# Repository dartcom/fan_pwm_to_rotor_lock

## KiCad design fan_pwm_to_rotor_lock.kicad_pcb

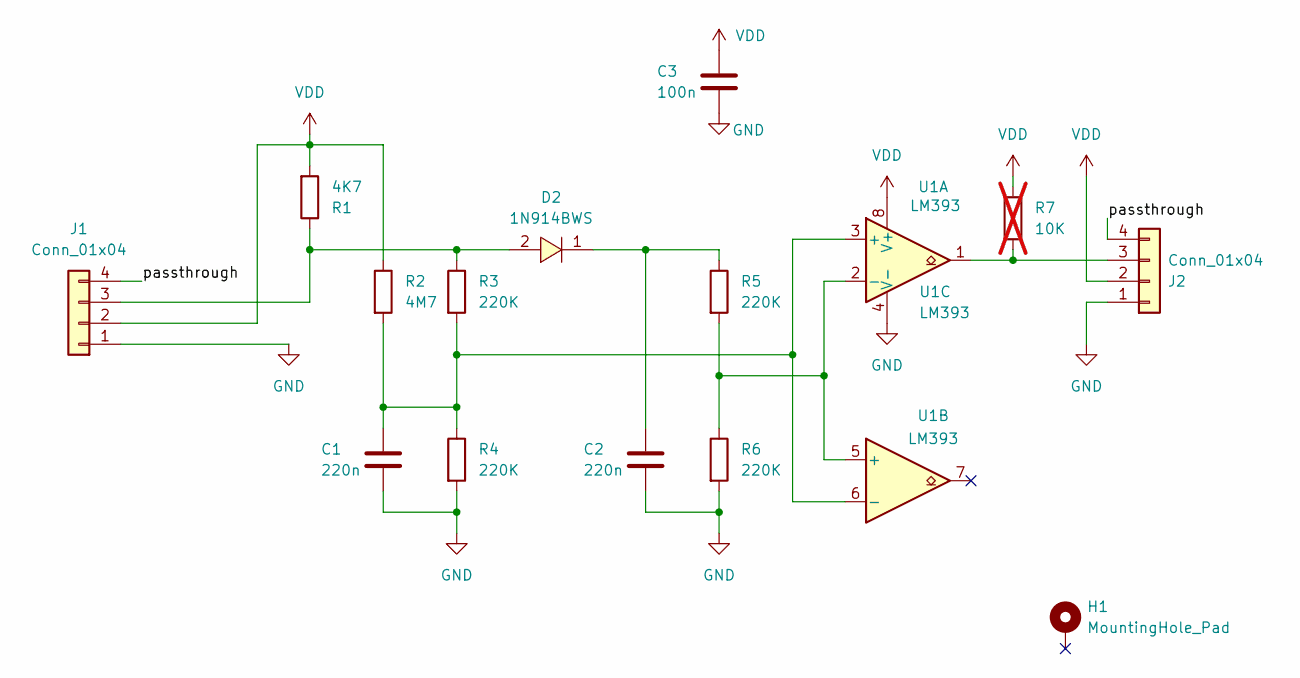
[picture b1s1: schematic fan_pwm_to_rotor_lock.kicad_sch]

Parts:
C1, C2: 220n; C_0805_2012Metric_Pad1.18x1.45mm_HandSolder
C3: 100n; C_0805_2012Metric_Pad1.18x1.45mm_HandSolder
D2: 1N914BWS; D_SOD-323_HandSoldering; LCSC Part C258181
H1: MountingHole_Pad; MountingHole_3.2mm_M3_Pad_Via
J1, J2: Conn_01x04; FanPinHeader_1x04_P2.54mm_Vertical
R1: 4K7; R_0805_2012Metric_Pad1.20x1.40mm_HandSolder
R2: 4M7; R_0805_2012Metric_Pad1.20x1.40mm_HandSolder
R3, R4, R5, R6: 220K; R_0805_2012Metric_Pad1.20x1.40mm_HandSolder
R7: 10K; R_0805_2012Metric_Pad1.20x1.40mm_HandSolder; not fitted
U1: LM393; SSOP-8_2.95x2.8mm_P0.65mm

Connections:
/passthrough: J1.4, J2.4
GND: C1.2, C2.2, C3.2, J1.1, J2.1, R4.2, R6.2, U1.4 (V-)
unnamed: C2.1, D2.1, R5.1
unnamed: D2.2, J1.3, R1.1, R3.1
unnamed: J2.3, R7.2, U1.1
unnamed: C1.1, R2.2, R3.2, R4.1, U1.3 (+), U1.6 (-)
unnamed: R5.2, R6.1, U1.2 (-), U1.5 (+)
VDD: C3.1, J1.2, J2.2, R1.2, R2.1, R7.1, U1.8 (V+)

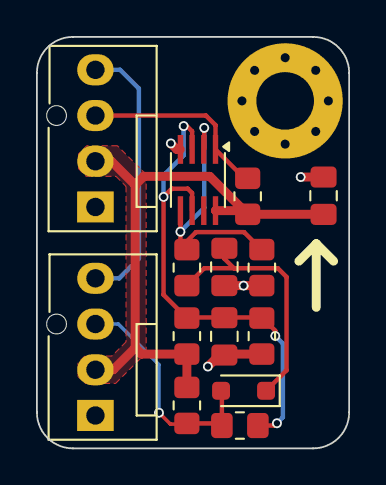
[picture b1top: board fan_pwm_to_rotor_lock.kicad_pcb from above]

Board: 2 copper layers, 17.3 x 22.9 mm, 15 parts (0 on the bottom side), 8 nets.

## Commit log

2025-02-14 kaliva ton pairneis
2025-08-05 Fix incorrect pin assignment
